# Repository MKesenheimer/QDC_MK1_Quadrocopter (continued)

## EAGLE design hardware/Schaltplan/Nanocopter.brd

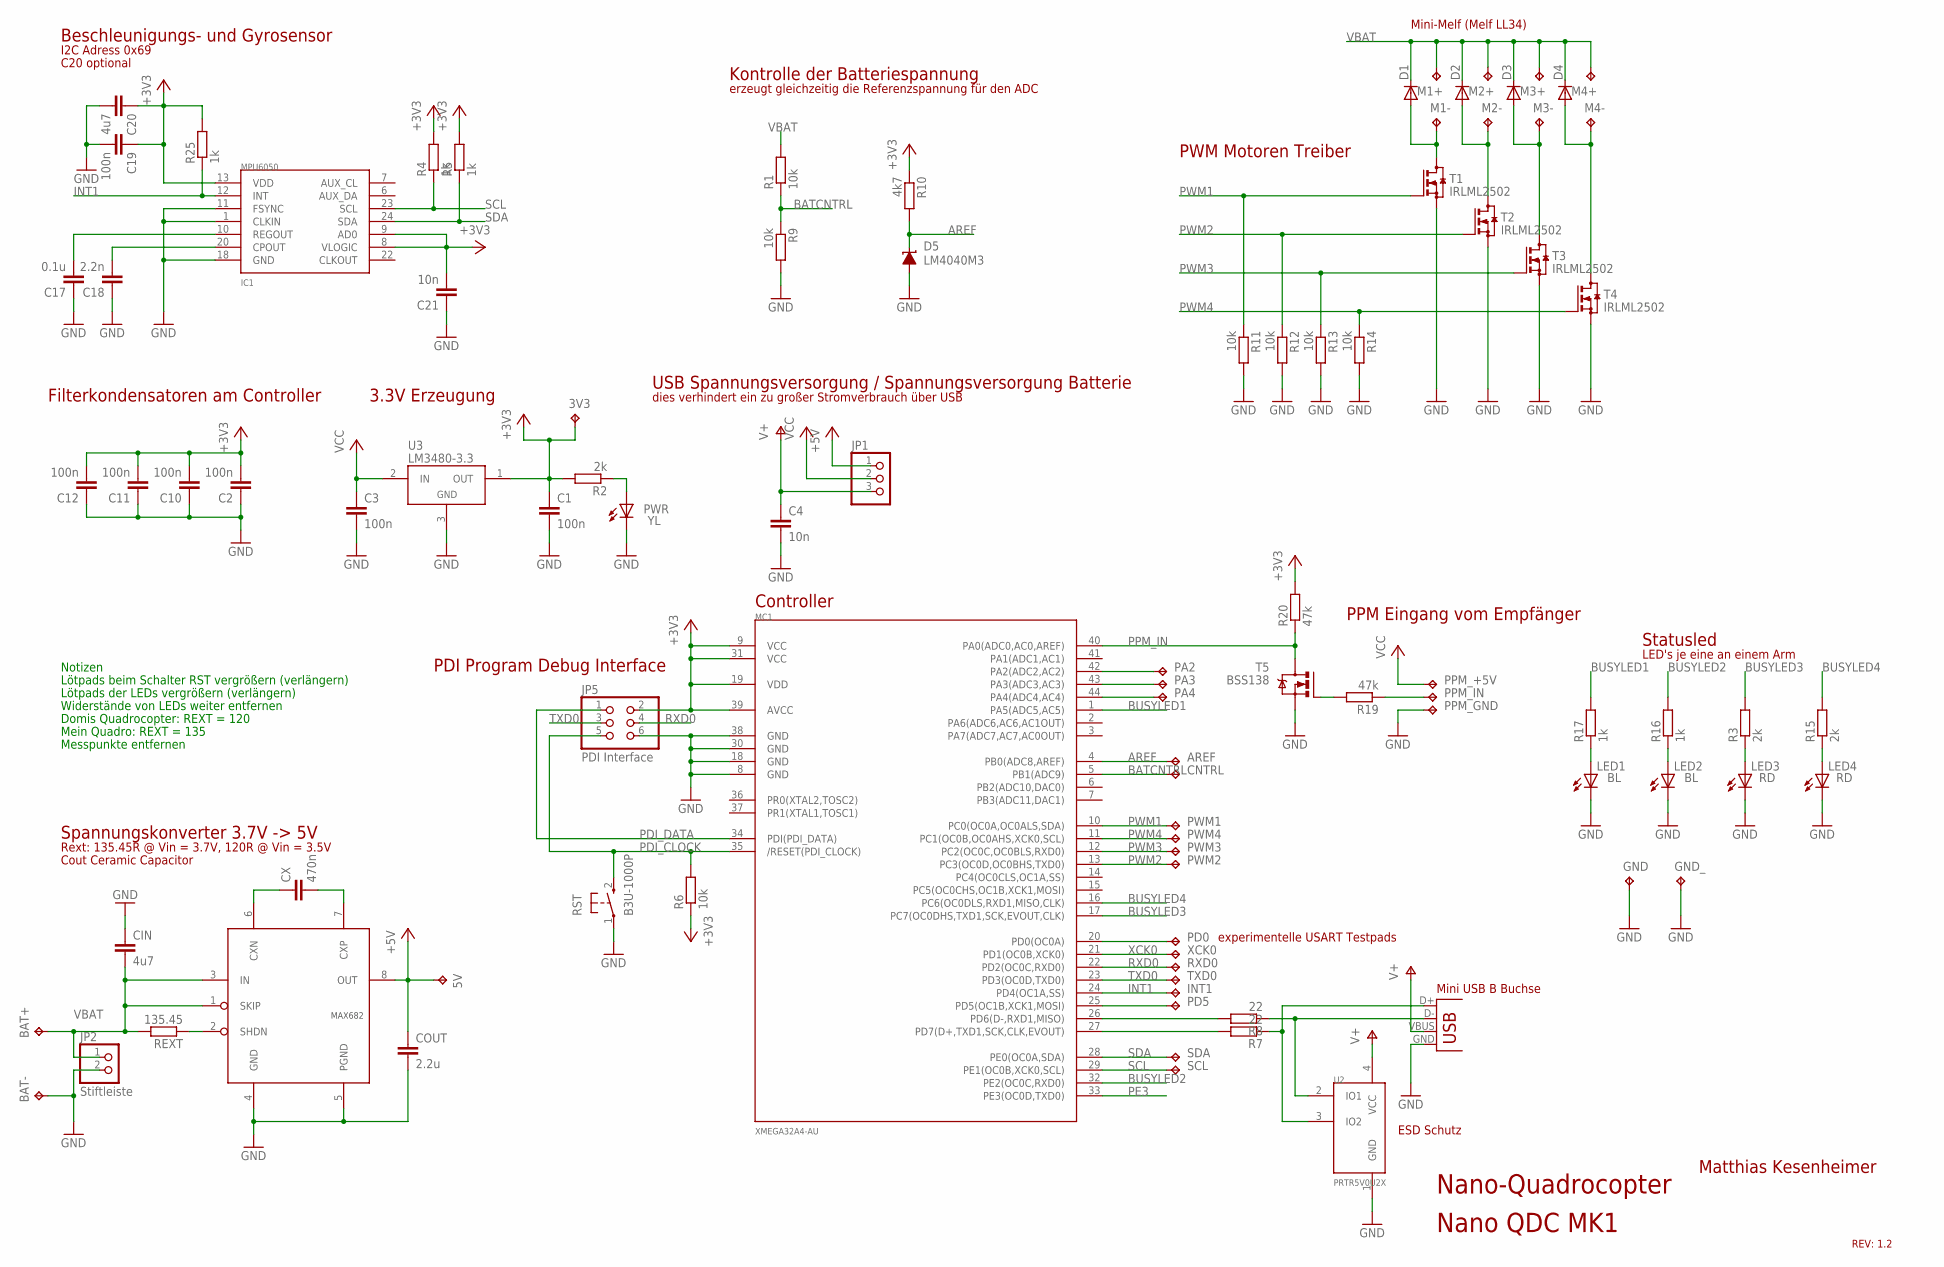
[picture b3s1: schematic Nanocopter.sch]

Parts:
3V3, 5V: TPTP12SQ; TP12SQ
AREF: TPTP10SQ; TP10SQ
BAT+: TPTP12SQ; TP12SQ
BAT-: TPTP12SQ; TP12SQ
C1, C2, C3, C10, C11, C12, C19: 100n; C0603
C4, C21: 10n; C0603
C17: 0.1u; C0603
C18: 2.2n; C0603
C20: 4u7; C0603
CIN: 4u7; C1206
CNTRL: TPTP10SQ; TP10SQ
COUT: 2.2u; C1206
CX: 470n; C0603
D1, D2, D3, D4: DIODE-MINIMELF; MINIMELF
D5: LM4040M3; SOT-23
GND: TPTP12SQ; TP12SQ
GND_: TPTP12SQ; TP12SQ
IC1: MPU6050; QFN-24
INT1: TPTP10SQ; TP10SQ
JP1: PINHD-1X3; 1X03
JP2: Stiftleiste; 1X02
JP5: PDI Interface; 2X03
LED1, LED2: BL; CHIPLED_0603
LED3, LED4: RD; CHIPLED_0603
M1+, M1-, M2+, M2-, M3+, M3-, M4+, M4-: TPTP15SQ; TP15SQ
MC1: XMEGA32A4-AU; TQFP44
PA2, PA3, PA4: TPTP10SQ; TP10SQ
PD0, PD5: TPTP10SQ; TP10SQ
PPM_+5V: TPTP10SQ; TP10SQ
PPM_GND: TPTP10SQ; TP10SQ
PPM_IN: TPTP10SQ; TP10SQ
PWM1, PWM2, PWM3, PWM4: TPTP10SQ; TP10SQ
PWR: YL; CHIPLED_0603
R1, R6, R9, R11, R12, R13, R14: 10k; R0603
R2, R3, R15: 2k; R0603
R4, R5, R16, R17, R25: 1k; R0603
R7, R8: 22; R0603
R10: 4k7; R0603
R19, R20: 47k; R0603
REXT: 135.45; R0603
RST: B3U-1000P; SW_SMD
RXD0: TPTP10SQ; TP10SQ
SCL: TPTP10SQ; TP10SQ
SDA: TPTP10SQ; TP10SQ
T1, T2, T3, T4: IRLML2502; SOT23
T5: BSS138; SOT23
TXD0: TPTP10SQ; TP10SQ
U1: MAX682; SOIC(N)8
U2: PRTR5V0U2X; SOT143B
U3: LM3480-3.3; SOT-23-3
X1: USBSMD; USB-MINIB
XCK0: TPTP10SQ; TP10SQ

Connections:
+3V3: 3V3.TP, C1.1, C2.2, C10.2, C11.2, C12.2, C19.1, C20.1, C21.2, IC1.8 (VLOGIC), IC1.9 (AD0), IC1.13 (VDD), JP5.2, MC1.9 (VCC), MC1.19 (VDD), MC1.31 (VCC), MC1.39 (AVCC), R2.2, R4.2, R5.2, R6.1, R10.1, R20.2, R25.2, U3.1 (OUT)
+5V: 5V.TP, COUT.1, JP1.1, U1.8 (OUT)
AREF: AREF.TP, D5.1 (C), MC1.4 (PB0(ADC8,AREF)), R10.2
BATCNTRL: CNTRL.TP, MC1.5 (PB1(ADC9)), R1.1, R9.1
BUSYLED1: MC1.1 (PA5(ADC5,AC5)), R17.2
BUSYLED2: MC1.32 (PE2(OC0C,RXD0)), R16.2
BUSYLED3: MC1.17 (PC7(OC0DHS,TXD1,SCK,EVOUT,CLK)), R3.2
BUSYLED4: MC1.16 (PC6(OC0DLS,RXD1,MISO,CLK)), R15.2
D+: MC1.27 (PD7(D+,TXD1,SCK,CLK,EVOUT)), R7.2
D-: MC1.26 (PD6(D-,RXD1,MISO)), R8.2
GND: BAT-.TP, C1.2, C2.1, C3.2, C4.2, C10.1, C11.1, C12.1, C17.1, C18.1, C19.2, C20.2, C21.1, CIN.1, COUT.2, D5.2 (A), GND.TP, GND_.TP, IC1.1 (CLKIN), IC1.11 (FSYNC), IC1.18 (GND), JP2.2, JP5.6, LED1.C, LED2.C, LED3.C, LED4.C, MC1.8 (GND), MC1.18 (GND), MC1.30 (GND), MC1.38 (GND), PPM_GND.TP, PWR.C, R9.2, R11.2, R12.2, R13.2, R14.2, RST.1, T1.2 (S), T2.2 (S), T3.2 (S), T4.2 (S), T5.2 (S), U1.4 (GND), U1.5 (PGND), U2.1 (GND), U3.3 (GND), X1.GND
INT1: IC1.12 (INT), INT1.TP, MC1.24 (PD4(OC1A,SS)), R25.1
unnamed: R19.2, T5.1 (G)
unnamed: PPM_IN.TP, R19.1
unnamed: MC1.44 (PA4(ADC4,AC4)), PA4.TP
unnamed: CX.1, U1.6 (CXN)
unnamed: MC1.43 (PA3(ADC3,AC3)), PA3.TP
unnamed: MC1.42 (PA2(ADC2,AC2)), PA2.TP
unnamed: PWR.A, R2.1
unnamed: LED3.A, R3.1
unnamed: REXT.1, U1.2 (SHDN)
unnamed: CX.2, U1.7 (CXP)
unnamed: LED4.A, R15.1
unnamed: LED2.A, R16.1
unnamed: LED1.A, R17.1
unnamed: D1.A, M1-.TP, T1.3 (D)
unnamed: D3.A, M3-.TP, T3.3 (D)
unnamed: D4.A, M4-.TP, T4.3 (D)
unnamed: C17.2, IC1.10 (REGOUT)
unnamed: C18.2, IC1.20 (CPOUT)
unnamed: D2.A, M2-.TP, T2.3 (D)
unnamed: MC1.20 (PD0(OC0A)), PD0.TP
unnamed: MC1.25 (PD5(OC1B,XCK1,MOSI)), PD5.TP
PDI_CLOCK: JP5.5, MC1.35 (/RESET(PDI_CLOCK)), R6.2, RST.2
PDI_DATA: JP5.1, MC1.34 (PDI(PDI_DATA))
PE3: MC1.33 (PE3(OC0D,TXD0))
PPM_IN: MC1.40 (PA0(ADC0,AC0,AREF)), R20.1, T5.3 (D)
PWM1: MC1.10 (PC0(OC0A,OC0ALS,SDA)), PWM1.TP, R11.1, T1.1 (G)
PWM2: MC1.13 (PC3(OC0D,OC0BHS,TXD0)), PWM2.TP, R12.1, T2.1 (G)
PWM3: MC1.12 (PC2(OC0C,OC0BLS,RXD0)), PWM3.TP, R13.1, T3.1 (G)
PWM4: MC1.11 (PC1(OC0B,OC0AHS,XCK0,SCL)), PWM4.TP, R14.1, T4.1 (G)
RXD0: JP5.4, MC1.22 (PD2(OC0C,RXD0)), RXD0.TP
SCL: IC1.23 (SCL), MC1.29 (PE1(OC0B,XCK0,SCL)), R4.1, SCL.TP
SDA: IC1.24 (SDA), MC1.28 (PE0(OC0A,SDA)), R5.1, SDA.TP
TXD0: JP5.3, MC1.23 (PD3(OC0D,TXD0)), TXD0.TP
USB+: R7.1, U2.3 (IO2), X1.D+
USB-: R8.1, U2.2 (IO1), X1.D-
V+: C4.1, JP1.3, U2.4 (VCC), X1.VBUS
VBAT: BAT+.TP, CIN.2, D1.C, D2.C, D3.C, D4.C, JP2.1, M1+.TP, M2+.TP, M3+.TP, M4+.TP, R1.2, REXT.2, U1.1 (SKIP), U1.3 (IN)
VCC: C3.1, JP1.2, PPM_+5V.TP, U3.2 (IN)
XCK0: MC1.21 (PD1(OC0B,XCK0)), XCK0.TP

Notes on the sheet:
Rext: 135.45R @ Vin = 3.7V, 120R @ Vin = 3.5V
Cout Ceramic Capacitor
I2C Adress 0x69
Beschleunigungs- und Gyrosensor
PWM Motoren Treiber
PPM Eingang vom Empfänger
Spannungskonverter 3.7V -> 5V
USB Spannungsversorgung / Spannungsversorgung Batterie
3.3V Erzeugung
Statusled
PDI Program Debug Interface
Matthias Kesenheimer
REV: 1.2
Nano-Quadrocopter
Nano QDC MK1
Mini USB B Buchse
dies verhindert ein zu großer Stromverbrauch über USB
Controller
Filterkondensatoren am Controller
C20 optional
Kontrolle der Batteriespannung
erzeugt gleichzeitig die Referenzspannung für den ADC
LED's je eine an einem Arm
ESD Schutz
experimentelle USART Testpads
Mini-Melf (Melf LL34)
Notizen
Lötpads beim Schalter RST vergrößern (verlängern)
Lötpads der LEDs vergrößern (verlängern)
Widerstände von LEDs weiter entfernen
Domis Quadrocopter: REXT = 120
Mein Quadro: REXT = 135
Messpunkte entfernen

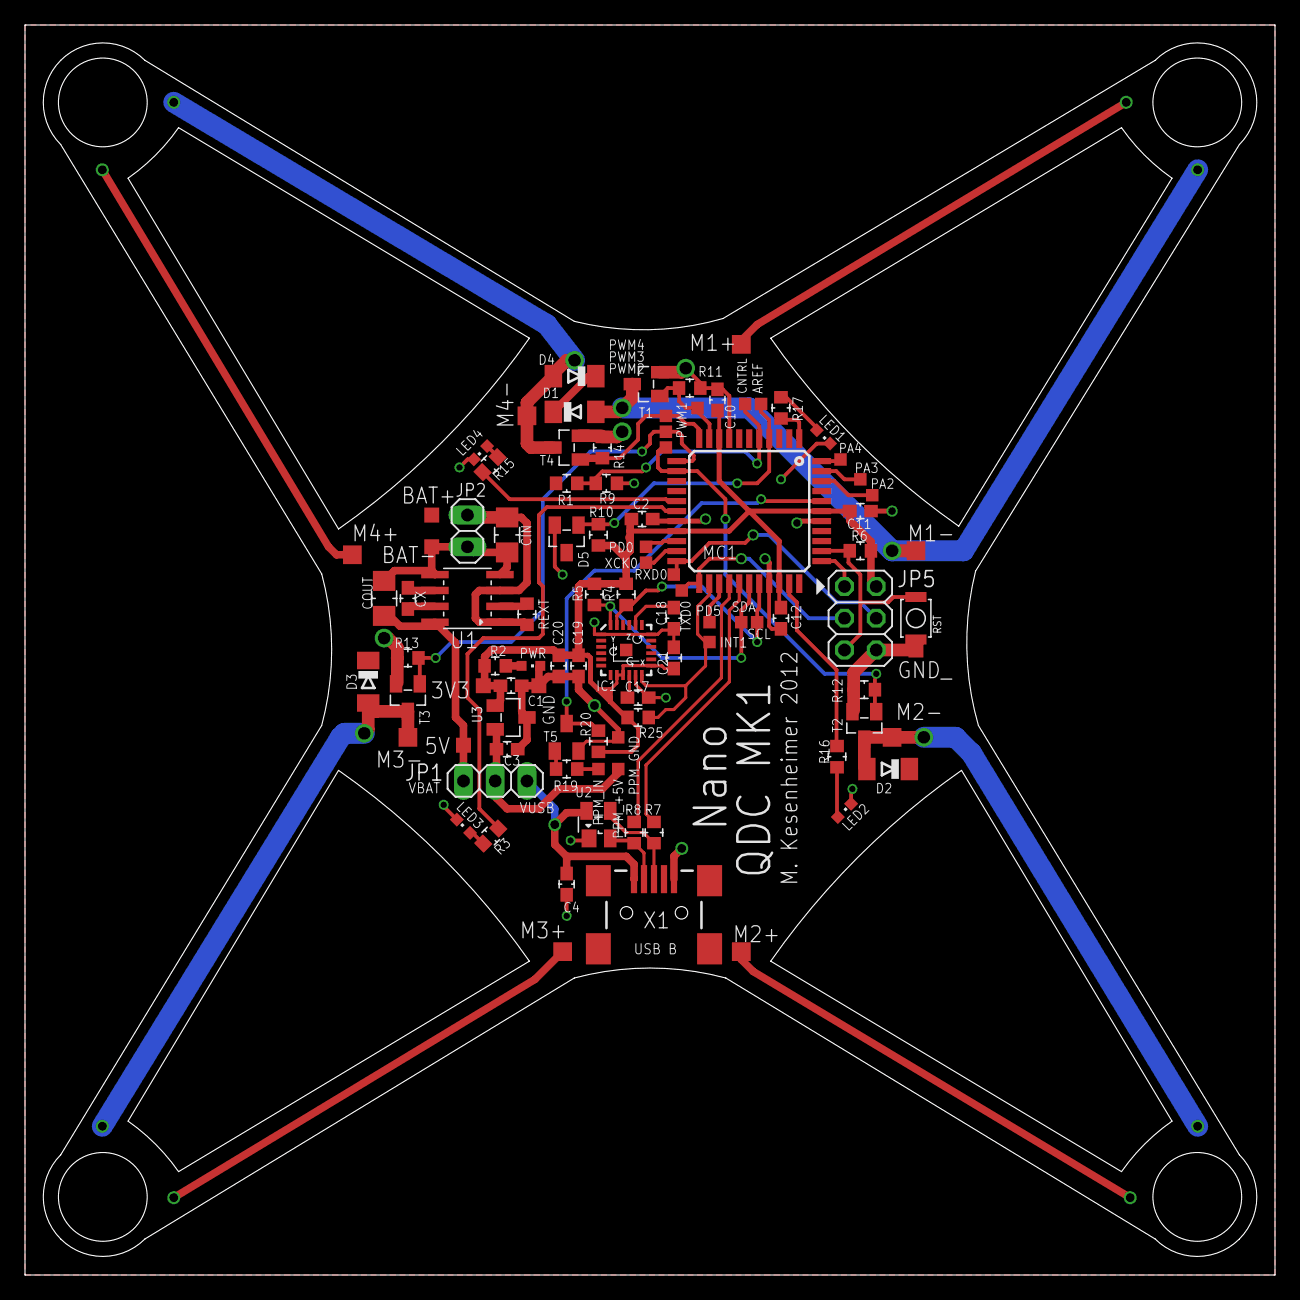
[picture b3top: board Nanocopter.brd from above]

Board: 2 copper layers, 100.0 x 100.0 mm, 95 parts (0 on the bottom side), 50 nets.

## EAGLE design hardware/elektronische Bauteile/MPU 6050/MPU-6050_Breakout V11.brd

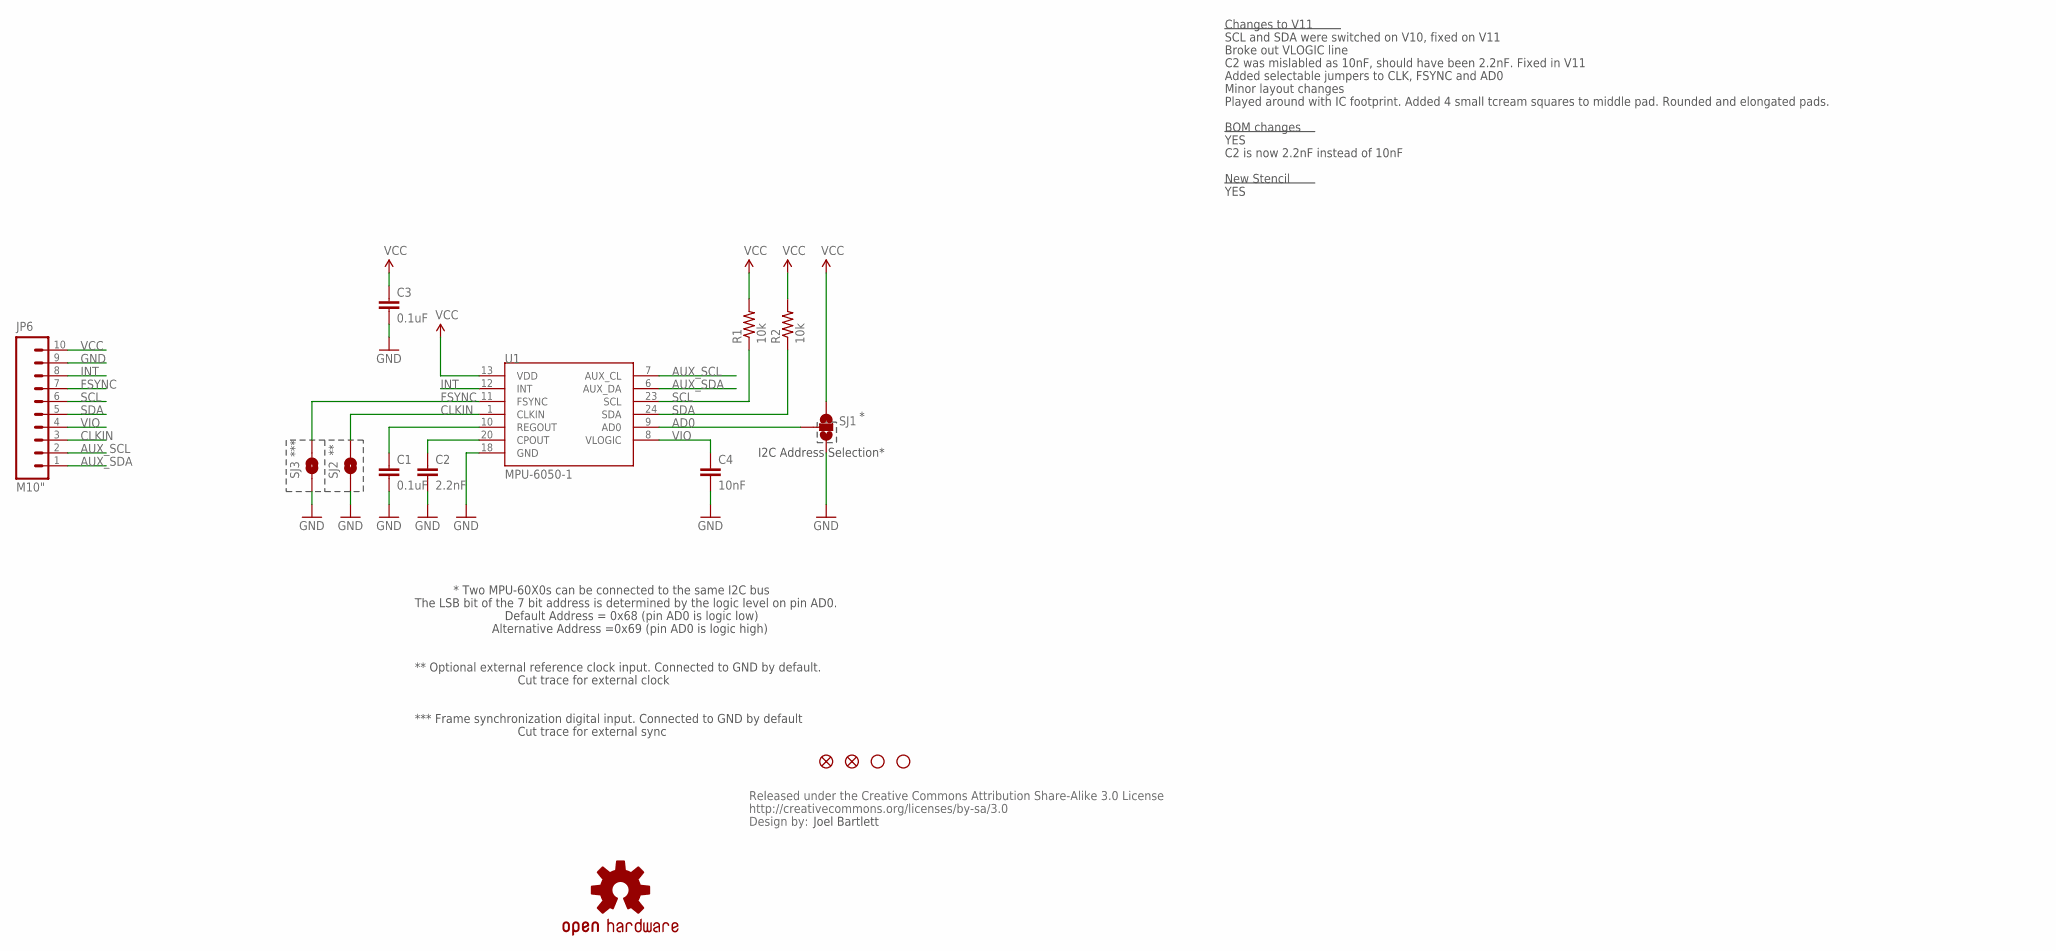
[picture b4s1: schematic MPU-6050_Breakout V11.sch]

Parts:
C1, C3: 0.1uF; 0402-CAP
C2: 2.2nF; 0402-CAP
C4: 10nF; 0402-CAP
JP2, JP5: FIDUCIALUFIDUCIAL; MICRO-FIDUCIAL
JP3, JP4: STAND-OFFTIGHT; STAND-OFF-TIGHT
JP6: M10"; 1X10
R1, R2: 10k; 0402-RES
SJ1: SOLDERJUMPER_2WAYPASTE2&3; SJ_3_PASTE2&3
SJ2, SJ3: SOLDERJUMPERTRACE; SJ_2S-TRACE
U1: MPU-6050-1; QFN-24-4MM2
U3: CREATIVE_COMMONS
U$1: OSHW-LOGOS; OSHW-LOGO-S

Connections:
AD0: SJ1.2, U1.9 (AD0)
AUX_SCL: JP6.2, U1.7 (AUX_CL)
AUX_SDA: JP6.1, U1.6 (AUX_DA)
CLKIN: JP6.3, SJ2.2, U1.1 (CLKIN)
FSYNC: JP6.7, SJ3.2, U1.11 (FSYNC)
GND: C1.2, C2.2, C3.2, C4.2, JP6.9, SJ1.3, SJ2.1, SJ3.1, U1.18 (GND)
INT: JP6.8, U1.12 (INT)
unnamed: C2.1, U1.20 (CPOUT)
unnamed: C1.1, U1.10 (REGOUT)
SCL: JP6.6, R1.1, U1.23 (SCL)
SDA: JP6.5, R2.1, U1.24 (SDA)
VCC: C3.1, JP6.10, R1.2, R2.2, SJ1.1, U1.13 (VDD)
VIO: C4.1, JP6.4, U1.8 (VLOGIC)

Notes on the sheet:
Joel Bartlett
I2C Address Selection*
*** Frame synchronization digital input. Connected to GND by default
***
Cut trace for external sync
* Two MPU-60X0s can be connected to the same I2C bus
Default Address = 0x68 (pin AD0 is logic low)
Alternative Address =0x69 (pin AD0 is logic high)
The LSB bit of the 7 bit address is determined by the logic level on pin AD0.
** Optional external reference clock input. Connected to GND by default.
Cut trace for external clock
Changes to V11
SCL and SDA were switched on V10, fixed on V11
C2 was mislabled as 10nF, should have been 2.2nF. Fixed in V11
Broke out VLOGIC line
BOM changes
New Stencil
YES
C2 is now 2.2nF instead of 10nF
Minor layout changes
Added selectable jumpers to CLK, FSYNC and AD0
Played around with IC footprint. Added 4 small tcream squares to middle pad. Rounded and elongated pads.

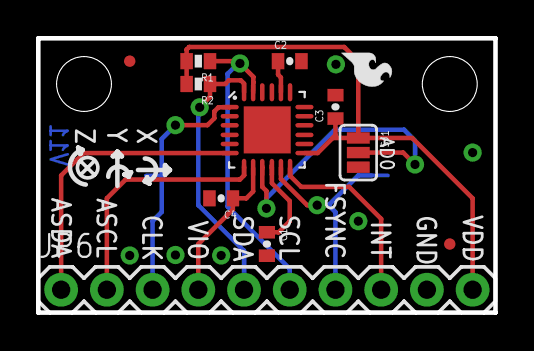
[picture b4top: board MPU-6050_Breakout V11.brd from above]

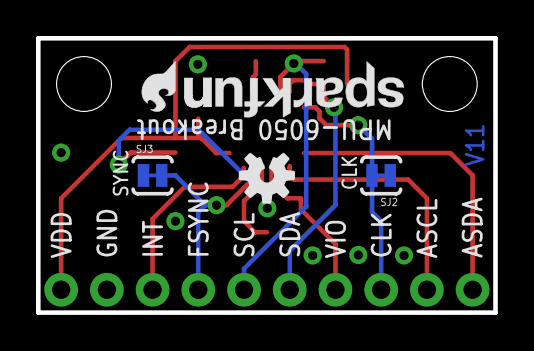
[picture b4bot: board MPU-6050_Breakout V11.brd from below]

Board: 2 copper layers, 25.4 x 15.2 mm, 20 parts (5 on the bottom side), 13 nets.

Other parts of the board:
U$2, U$3: SFE-LOGO-FLAME
U$4: SFE-NEW-WEB

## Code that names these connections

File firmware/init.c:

/*
 QDC MK1 v1.0 - September 2014
 http://deralchemist.wordpress.com/
 Copyright (c) 2014 Matthias Kesenheimer.  All rights reserved.
 An Open Source Arduino based multicopter.
 
 This program is free software: you can redistribute it and/or modify
 it under the terms of the GNU General Public License as published by
 the Free Software Foundation, either version 3 of the License, or
 (at your option) any later version.
 
 This program is distributed in the hope that it will be useful,
 but WITHOUT ANY WARRANTY; without even the implied warranty of
 MERCHANTABILITY or FITNESS FOR A PARTICULAR PURPOSE. See the
 GNU General Public License for more details.
 
 You should have received a copy of the GNU General Public License
 along with this program. If not, see <http://www.gnu.org/licenses/>.
 */

void initClock()
{
	OSC.CTRL = OSC_RC32MEN_bm;		//aktiviert internen 32MHz Oszillator
	while(!(OSC.STATUS & OSC_RC32MRDY_bm));	//warte bis der Oszillator stabil luft
	CCP = CCP_IOREG_gc;			//deaktiviert den Interrupt fr 4 Taktzyklen -> Schutz
	CLK.CTRL = 0x01;			//Waehle den Oszillator als Taktquelle aus
}

void initTimerE0() //Timer E0 loest alle 10 ms einen Interrupt aus (OVF_IRQ)
{
	//Timer E0 initialisieren
	TCE0.CTRLA = TC_CLKSEL_DIV64_gc;
	TCE0.CTRLB = 0x00;	//Timer im "Normalmode"
	//TCE0.INTCTRLA = 0x01;	//Interrupt hat niedrige Prioritt
	TCE0.INTCTRLA = 0x02;	//Interrupt hat mittlere Prioritt
	//TCE0.INTCTRLA = 0x03;	//Interrupt hat hohe Prioritt
	TCE0.PER = 5000;

	ms10 = 0;				//Variable, die die vergangenen Millisekunden in Zehnerschritten zaehlt
}

void initPWM()
{
	//Timer C0 als PWM initialisieren
	TCC0.PER = 0xefff;		//ganzer Zaehlerbereich wird verwendet
	TCC0.CTRLA = 0x01;		//Prescaler auf 2
	TCC0.CTRLB = 0xf3;		//Single Slope und PWM an allen PWM Ausgaengen freischalten
	
    motor[0] = MOTORMIN;
    motor[1] = MOTORMIN;
    motor[2] = MOTORMIN;
    motor[3] = MOTORMIN;
}

void initPorts()
{
	//initialisierung der Motorenausgnge
	PORTC.DIR |= (1<<PIN0);		//Motor 1
	PORTC.DIR |= (1<<PIN1);		//Motor 2
	PORTC.DIR |= (1<<PIN2);		//Motor 3
	PORTC.DIR |= (1<<PIN3);		//Motor 4
	
	//LEDs definieren
	PORTA.DIR |= (1<<PIN5);		//blau an Motor 1 = LED1= PORTA.DIR = 0x20;
	PORTC.DIR |= (1<<PIN6);		//rot an Motor 2 = LED2
	PORTC.DIR |= (1<<PIN7);		//rot an Motor 3 = LED3
	PORTE.DIR |= (1<<PIN2);		//blau an Motor 4 = LED4
	
	//TWI Ausgnge - Noetig?
	PORTE.DIRSET = PIN0_bm;      // Als Ausgang  TWI SDA
	PORTE.DIRSET = PIN1_bm;       // Als Ausgang  TWI SCL
	
	//RECEIVER UART D0
	PORTD.DIRCLR = PIN2_bm;		//Empfangen RxD0
	PORTD.DIRSET = PIN3_bm;		//Senden TxD0
	
	//DEBUG GUI UART D1
	PORTD.DIRSET = PIN7_bm;		//Pin7 D+ TxD1
	PORTD.DIRCLR = PIN6_bm;		//Pin6 D- RxD1
}

void initMPU6050()
{
	//Device Reset
	sendbuffer[0] = MPU6050_RA_PWR_MGMT_1;	//Registeradresse 0x6b
	sendbuffer[1] = 0x80;	//Device Reset
	TWI_MasterWrite(&twiMaster, SLAVE_ADDRESS, &sendbuffer[0], 2);
      while (twiMaster.status != TWIM_STATUS_READY){}
	
	//_delay_ms(10);
	_delay_loop_2(65535);	// 8,2 ms
      
	//PWR_MGMT_1
	sendbuffer[0] = MPU6050_RA_PWR_MGMT_1;	//Registeradresse 0x6b
	sendbuffer[1] = 0x03;	//DEVICE_RESET = 0, SLEEP = 0, CYCLE = 0, TEMP_DIS = 0, CLKSEL = PLL with z axis gyro reference
	TWI_MasterWrite(&twiMaster, SLAVE_ADDRESS, &sendbuffer[0], 2);
	while (twiMaster.status != TWIM_STATUS_READY){}
	
	
	//Sample Rate 1000/(1+1) =  500Hz
	sendbuffer[0] = MPU6050_RA_SMPLRT_DIV;	//Registeradresse 0x19
	sendbuffer[1] = 0x01;
	TWI_MasterWrite(&twiMaster, SLAVE_ADDRESS, &sendbuffer[0], 2);
	while (twiMaster.status != TWIM_STATUS_READY){}
	
	
	//DLPF
	sendbuffer[0] = MPU6050_RA_CONFIG; //Registeradresse 0x1a
	sendbuffer[1] = MPU6050_DLPF_CFG_42HZ;	//EXT_SYNC_SET = 0, Digital Low Pass Filter, Auswahl 5, 10, 20, 42, 98, 188, 256Hz
	TWI_MasterWrite(&twiMaster, SLAVE_ADDRESS, &sendbuffer[0], 2);
	while (twiMaster.status != TWIM_STATUS_READY){}
}

void initGyro()
{	
	//GYRO_CONFIG
	sendbuffer[0] = MPU6050_RA_GYRO_CONFIG;  //Registeradresse 0x1b
	sendbuffer[1] = 0b00001000;	//Gyro Selftest FS_SEL = disabled, Scale +-500 deg/sec
	TWI_MasterWrite(&twiMaster, SLAVE_ADDRESS, &sendbuffer[0], 2);
	while (twiMaster.status != TWIM_STATUS_READY){}
}

void initAcc()
{
	//ACCEL_CONFIG
	sendbuffer[0] = MPU6050_RA_ACCEL_CONFIG;
	sendbuffer[1] = 0b00001000;	//Accel Selftest = disabled, Scale = +-4g, DHPF = disabled
	TWI_MasterWrite(&twiMaster, SLAVE_ADDRESS, &sendbuffer[0], 2);
	while (twiMaster.status != TWIM_STATUS_READY){}	
}

void initSensors()
{
	//_delay_ms(300);
      for (a=0; a<3; a++) {_delay_loop_2(65535);}	// ca. 30 ms
	initMPU6050();
	initGyro();
	initAcc();
	//_delay_ms(300);
      for (a=0; a<3; a++) {_delay_loop_2(65535);}	// ca. 30 ms
}

void initUsart()
{
	//PMIC.CTRL |= PMIC_LOLVLEX_bm; //weglassen?

      //DEBUG GUI UART D1
      USARTD1.BAUDCTRLB = (BAUD_PRESCALED1 >> 8);
      USARTD1.BAUDCTRLA = BAUD_PRESCALED1;
      USARTD1.CTRLA |= (USART_RXCINTLVL_LO_gc | USART_DREINTLVL_LO_gc | USART_RXCINTLVL1_bm);
      USARTD1.CTRLB |= (USART_TXEN_bm | USART_RXEN_bm);
      USARTD1.CTRLC |= (USART_CMODE_ASYNCHRONOUS_gc | USART_PMODE_DISABLED_gc | USART_CHSIZE_8BIT_gc);

      //Quadrocopter mit DSM2/Spektrum Empfnger
      USARTD0.BAUDCTRLA = BAUD_PRESCALED0;
      USARTD0.BAUDCTRLB = (BAUD_PRESCALED0 >> 8);
      USARTD0.CTRLA = USART_RXCINTLVL_HI_gc;
      USARTD0.CTRLB = USART_RXEN_bm;
      USARTD0.CTRLC = USART_CMODE_ASYNCHRONOUS_gc | USART_PMODE_DISABLED_gc | USART_CHSIZE_8BIT_gc | USART_SBMODE_bm; //Asynchron, no parity, 8 Bit Zeichengr§e, 2 Stop Bits
}

void setup()
{
	//Initialisierungen
	initClock();
	initPorts();
	EEpromInit();
	
	//Fuer DEBUG - Motoren ausschalten
#if 1
    initPWM();
#endif
	
	initTimerE0(); //TimerE0 ist dafr zustndig, dass jede 2us ein Interrupt ausgeloest wird
	TWI_MasterInit(&twiMaster, &TWIE, TWI_MASTER_INTLVL_HI_gc, TWI_BAUDSETTING);	// TWI am PortE initialisiert
	initUsart();
	
	//Interruptlevel freigeben
	PMIC.CTRL |= PMIC_LOLVLEN_bm | PMIC_MEDLVLEN_bm | PMIC_HILVLEN_bm;
	sei();
	
	//Wichtig: muss nach der Initialisierung der Interrupts durchgefuehrt werden!,
	//da die Initialisierung auf I2C-Interrupts zugreift
	initSensors();
	config(); //Configuration
	
	//_delay_ms(3000); //Der Quadro wartet 3 Sekunden, danach kalibriert er sich
      //for (a=0; a<4; a++) {_delay_loop_2(65535);}	// ca. 40 ms
	calibrate();
    
    //Watchdog initialisieren
    WDT_EnableAndSetTimeout();
    //while (1); //Test
}

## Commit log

2014-09-25 XCode Projekt bereinigt
2014-09-25 eagle Dateien bereinigt
2014-09-25 minor code improvements
2014-09-25 deleted .DS_Store
2014-09-25 .DS_Store banished
2014-09-25 Verbesserungen in serial.c
2014-09-27 Verbesserungen der GUI und unnuetzer Code entfernt
2014-09-27 work in progress
2014-09-28 Arbeit an der GUI
2014-09-28 Übermitteln von Statuswerten an die GUI hinzugefügt
2014-09-28 .gitignore update
2014-09-28 host software aktuallisiert
2014-09-28 bereinigt
2014-09-29 kleine Verbesserungen
2014-09-30 PID Werte eingestellt
2014-09-30 Test der PID Werte
2014-10-05 PWM Prescaler verringert
2014-10-05 Verbesserungen an der Hardware
2014-10-18 Arbeit an Schaltplan V2
2014-10-25 Vorbereitungen für Version 2
2014-10-27 Ideen
2015-03-28 Arbeit an V2
2015-03-31 Neuer Schaltplan V2.1. Die Schaltung wird jetzt in zwei Teile aufgeteilt: Flugcontroller (SimpleControl) und Motortreiber-platine (BaseFrame).
2015-03-31 Test
2015-03-31 Dimensionen von SimpleControl aktualisiert
2015-03-31 Arbeit an den Dimensionen
2015-03-31 Abmessungen geändert
